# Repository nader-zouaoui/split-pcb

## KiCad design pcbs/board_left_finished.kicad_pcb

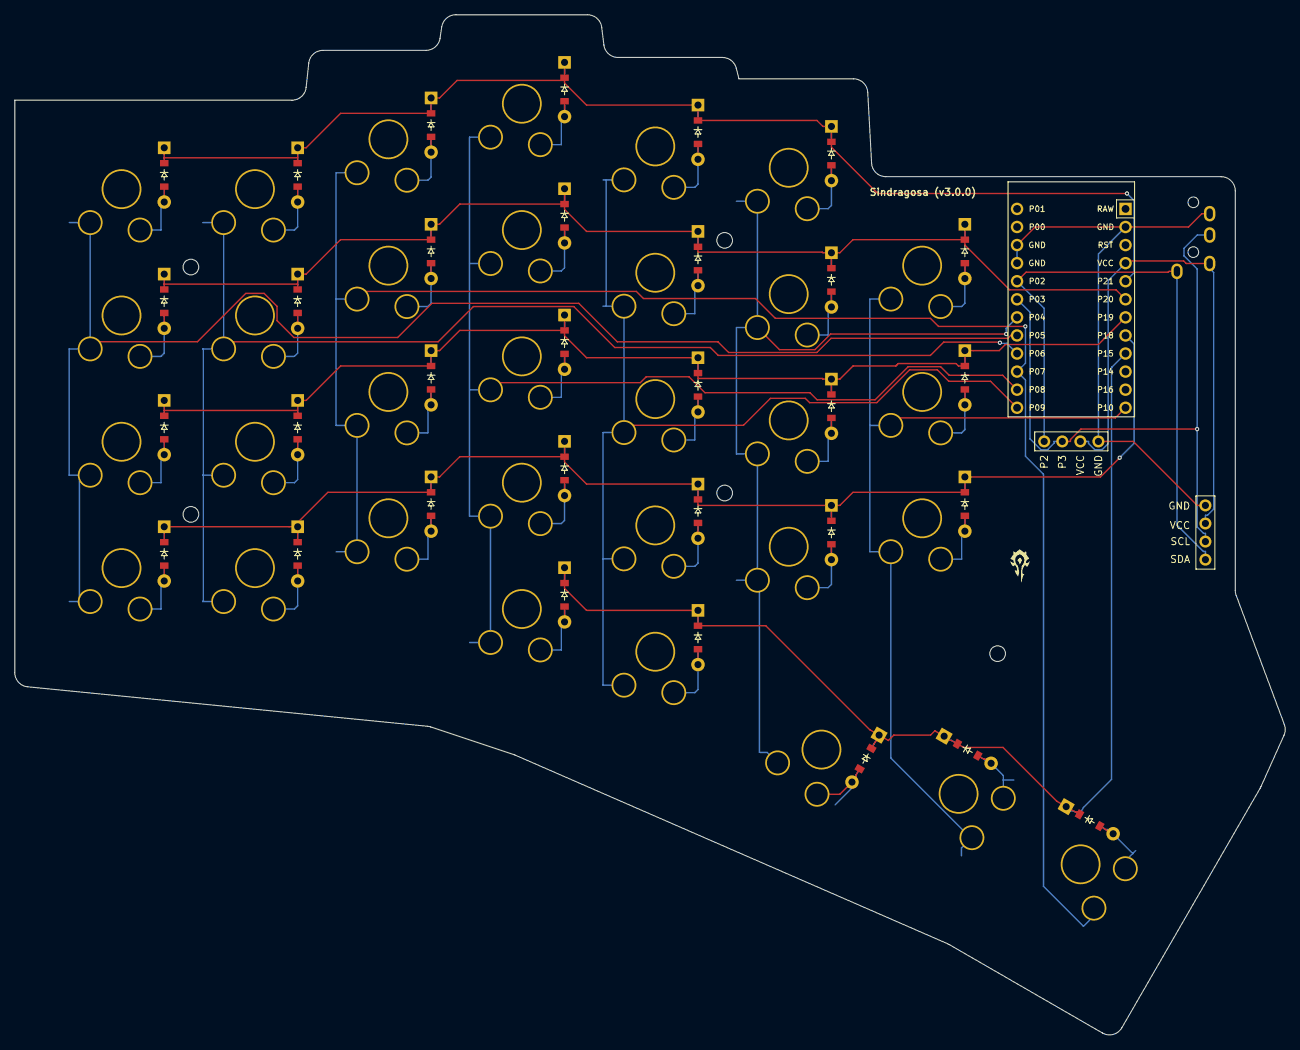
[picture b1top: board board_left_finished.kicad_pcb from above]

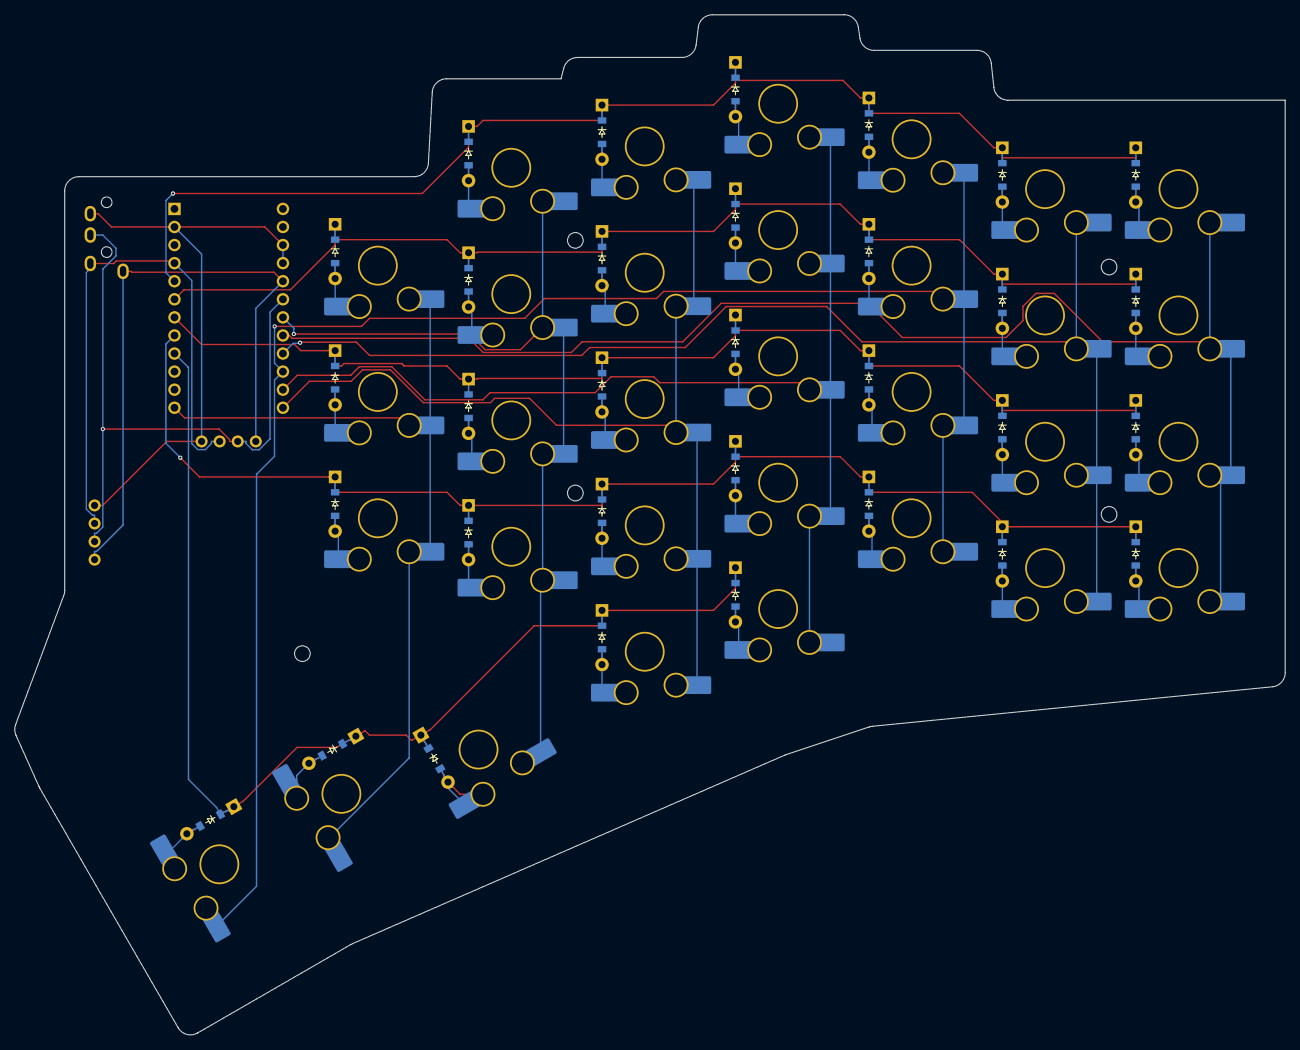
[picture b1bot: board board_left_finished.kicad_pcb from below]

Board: 2 copper layers, 178.5 x 143.3 mm, 73 parts (32 on the bottom side), 48 nets.

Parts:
D1, D2, D3, D4, D5, D6, D7, D8, D9, D10, D11, D12, D13, D14, D15, D16, D17, D18, D19, D20, D21, D22, D23, D24, D25, D26, D27, D28, D29, D30, D31, D32: ComboDiode
DISP1: display_ssd1306
I2COut: Val**; i2c-breakout
MCU1: ProMicro
MH1, MH2, MH3, MH4, MH5: mounting_hole_npth
S1, S2, S3, S4, S5, S6, S7, S8, S9, S10, S11, S12, S13, S14, S15, S16, S17, S18, S19, S20, S21, S22, S23, S24, S25, S26, S27, S28, S29, S30, S31, S32: switch_gateron_ks27_ks33
TRRS1: trrs_pj320a

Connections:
GND: DISP1.4, I2COut.1, MCU1.2, MCU1.15, MCU1.16, TRRS1.2
P2: DISP1.1, I2COut.4, MCU1.17, TRRS1.5
P3: DISP1.2, I2COut.3, MCU1.18, TRRS1.3
P4: MCU1.19, S23.1, S24.1, S25.1, S26.1, S30.1
P5: MCU1.20, S1.1, S2.1, S3.1, S4.1
P6: MCU1.21, S5.1, S6.1, S7.1, S8.1
P7: MCU1.22, S9.1, S10.1, S11.1, S12.1, S32.1
P8: MCU1.23, S13.1, S14.1, S15.1, S16.1, S17.1
P9: MCU1.24, S18.1, S19.1, S20.1, S21.1, S22.1
P10: MCU1.12, S27.1, S28.1, S29.1, S31.1
P15: D13.1, D18.1, D30.1, D31.1, D32.1, MCU1.9
P18: D1.1, D5.1, D9.1, D14.1, D19.1, D23.1, D27.1, MCU1.8
P19: D2.1, D6.1, D10.1, D15.1, D20.1, D24.1, D28.1, MCU1.7
P20: D3.1, D7.1, D11.1, D16.1, D21.1, D25.1, D29.1, MCU1.6
P21: D4.1, D8.1, D12.1, D17.1, D22.1, D26.1, MCU1.5
VCC: DISP1.3, I2COut.2, MCU1.4, TRRS1.4
big_thumb_cluster: D32.2, S32.2
fifth_bottom: D19.2, S19.2
fifth_home: D20.2, S20.2
fifth_mod: D18.2, S18.2
fifth_num: D22.2, S22.2
fifth_top: D21.2, S21.2
first_bottom: D1.2, S1.2
first_home: D2.2, S2.2
first_num: D4.2, S4.2
first_top: D3.2, S3.2
fourth_bottom: D14.2, S14.2
fourth_home: D15.2, S15.2
fourth_mod: D13.2, S13.2
fourth_num: D17.2, S17.2
fourth_top: D16.2, S16.2
medium_thumb_cluster: D31.2, S31.2
second_bottom: D5.2, S5.2
second_home: D6.2, S6.2
second_num: D8.2, S8.2
second_top: D7.2, S7.2
seventh_bottom: D27.2, S27.2
seventh_home: D28.2, S28.2
seventh_top: D29.2, S29.2
sixth_bottom: D23.2, S23.2
sixth_home: D24.2, S24.2
sixth_num: D26.2, S26.2
sixth_top: D25.2, S25.2
small_thumb_cluster: D30.2, S30.2
third_bottom: D9.2, S9.2
third_home: D10.2, S10.2
third_num: D12.2, S12.2
third_top: D11.2, S11.2

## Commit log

2026-01-28 feat: add finished board right
2026-01-28 feat: add board left
2026-01-28 add gerber files
